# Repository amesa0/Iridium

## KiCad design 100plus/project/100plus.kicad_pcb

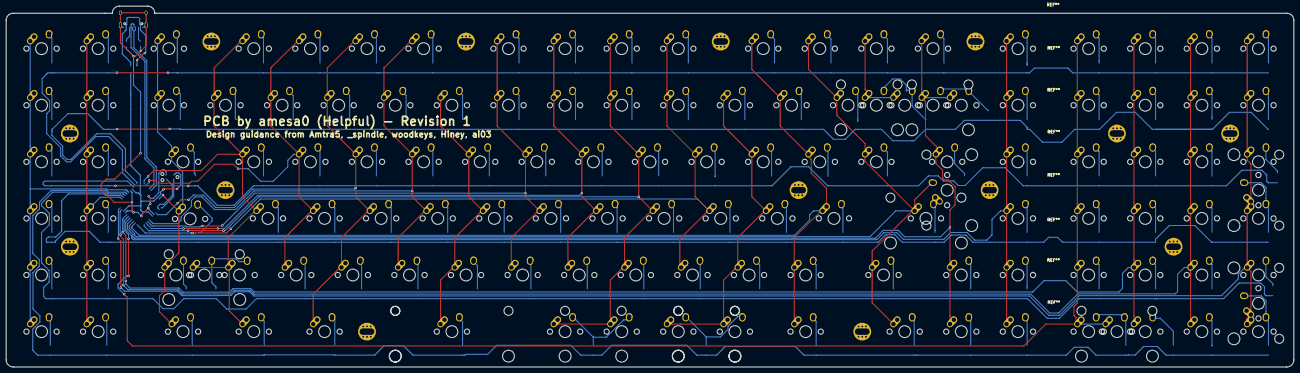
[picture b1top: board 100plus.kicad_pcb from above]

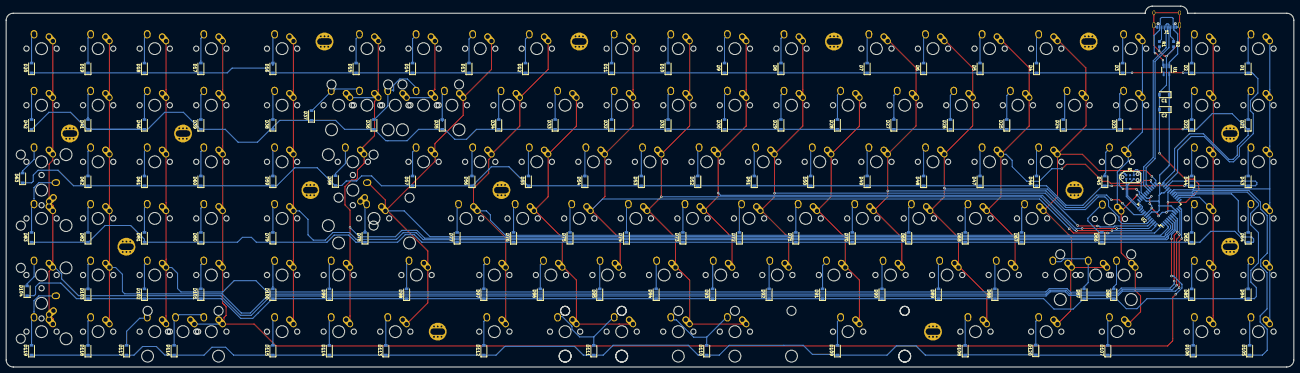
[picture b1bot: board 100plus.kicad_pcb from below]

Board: 2 copper layers, 433.4 x 121.4 mm, 258 parts (128 on the bottom side), 157 nets.

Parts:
C1: 10uf; D_SOD-123
C2: 0.4uf; D_SOD-123
D1, D2, D3, D4, D5, D6, D7, D8, D9, D10, D11, D12, D13, D14, D15, D16, D17, D18, D19, D20, D21, D22, D23, D24, D25, D26, D27, D28, D29, D30, D31, D32, D33, D34, D35, D36, D37, D38, D39, D40, D41, D42, D43, D44, D45, D46, D47, D48, D49, D50, D51, D52, D53, D54, D55, D56, D57, D58, D59, D60, D61, D62, D63, D64, D65, D66, D67, D68, D69, D70, D71, D72, D73, D74, D75, D76, D77, D78, D79, D80, D81, D82, D83, D84, D85, D86, D87, D88, D89, D90, D91, D92, D93, D94, D95, D96, D97, D98, D99, D100, D101, D102, D103, D104, D105, D106, D107, D108, D109, D110, D111, D112, D113, D114, D115, D116, D117, D118, D119, D120: D; D_SOD-123
J1: USB_Type_C_2.0_Receptacle; USB_TypeC_U31F-24SNA0201
K1, K2, K3, K4, K5, K6, K7, K8, K9, K10, K11, K12, K13, K14, K15, K16, K17, K18, K19, K20, K21, K22, K23, K24, K25, K26, K27, K28, K29, K30, K31, K32, K33, K34, K35, K36, K37, K38, K39, K40, K41, K42, K45, K46, K48, K49, K50, K51, K52, K53, K54, K55, K56, K57, K58, K59, K61, K62, K63, K64, K65, K67, K68, K70, K71, K72, K73, K74, K75, K76, K77, K78, K79, K80, K82, K83, K84, K85, K86, K87, K88, K91, K92, K93, K94, K95, K96, K97, K98, K99, K100, K102, K103, K104, K105, K106, K107, K108, K111, K112, K117, K119, K120, K121, K122, K123, K124, K125, K130: KEYSW; MX-1U-NoLED
K43, K44, K128, K129: KEYSW; MX-2U-NoLED
K47, K60, K113, K114, K118: KEYSW; MX-1.5U-NoLED
K66, K109: KEYSW; MX-2U-ReversedStabilizers-NoLED
K69, K101: KEYSW; MX-1.75U-NoLED
K81, K90: KEYSW; MX-2.25U-NoLED
K89: KEYSW; MX-1.25U-NoLED
K110: KEYSW; MX-7U-NoLED
K115, K116, K127: KEYSW; MX-3U-NoLED
K126: KEYSW; MX-6U-7UOverlay
P1: TC2030-IDC; TC2030-NL_SMALL
R1, R2: 5.1k; R_0603_1608Metric_Pad0.99x1.00mm_HandSolder
U1: MIC550X; SOT-23-5_HandSoldering
U2: ATXMEGA-A4U; TQFP-44_10x10mm_P0.8mm

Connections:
+5V: J1.A4, J1.B4, U1.1, U1.3
COL0: K1.1, K21.1, K45.1, K67.1, K87.1, K111.1, U2.17
COL1: K2.1, K22.1, K46.1, K68.1, K88.1, K112.1, U2.13
COL2: K3.1, K23.1, K47.1, K69.1, K89.1, K113.1, U2.32
COL3: K4.1, K24.1, K48.1, K70.1, K90.1, K108.1, K130.1, U2.23
COL4: K5.1, K25.1, K49.1, K71.1, K91.1, U2.24
COL5: K6.1, K26.1, K50.1, K72.1, K92.1, K114.1, U2.37
COL6: K7.1, K27.1, K51.1, K73.1, K93.1, U2.41
COL7: K8.1, K29.1, K53.1, K75.1, K95.1, U2.42
COL8: K9.1, K30.1, K54.1, K76.1, K96.1, U2.43
COL9: K10.1, K31.1, K55.1, K77.1, K97.1, K110.1, K116.1, U2.44
COL10: K11.1, K32.1, K56.1, K78.1, K98.1, U2.1
COL11: K12.1, K34.1, K58.1, K80.1, K100.1, K118.1, U2.2
COL12: K13.1, K35.1, K59.1, K81.1, K101.1, K119.1, K129.2, U2.3
COL13: K14.1, K36.1, K43.1
COL14: K15.1, K37.1, K44.1, K60.1, K102.1, K120.1, U2.4
COL15: K16.1, K38.1, K61.1, K82.1, K103.1, K121.1, U2.5
COL16: K17.1, K39.1, K62.1, K83.1, K104.1, K122.1, K128.1, U2.6
COL17: K18.1, K40.1, K63.1, K84.1, K105.1, K123.1, U2.7
COL18: K19.1, K41.1, K64.1, K85.1, K106.1, K124.1, U2.10
COL19: K20.1, K42.1, K65.1, K66.1, K86.1, K107.1, K109.1, K125.1, U2.11
GND: C1.2, C2.2, J1.A1, J1.B1, J1.S1, P1.6, R1.2, R2.2, U1.2, U2.8, U2.18, U2.30, U2.38
unnamed: D1.2, K1.2
unnamed: D2.2, K2.2
unnamed: D3.2, K3.2
unnamed: D4.2, K4.2
unnamed: D5.2, K5.2
unnamed: D6.2, K6.2
unnamed: D7.2, K7.2
unnamed: D8.2, K8.2
unnamed: D9.2, K9.2
unnamed: D10.2, K10.2
unnamed: D11.2, K11.2
unnamed: D12.2, K12.2
unnamed: D13.2, K13.2
unnamed: D14.2, K14.2
unnamed: D15.2, K15.2
unnamed: D16.2, K16.2
unnamed: D17.2, K17.2
unnamed: D18.2, K18.2
unnamed: D19.2, K19.2
unnamed: D20.2, K20.2
unnamed: D21.2, K21.2
unnamed: D22.2, K22.2
unnamed: D23.2, K23.2
unnamed: D24.2, K24.2
unnamed: D25.2, K25.2
unnamed: D26.2, K26.2
unnamed: D27.2, K27.2
unnamed: D28.2, K28.2
unnamed: D29.2, K29.2
unnamed: D30.2, K30.2
unnamed: D31.2, K31.2
unnamed: D32.2, K32.2
unnamed: D33.2, K33.2
unnamed: D34.2, K34.2
unnamed: D35.2, K35.2
unnamed: D36.2, K36.2, K43.2
unnamed: D37.2, K37.2, K44.2
unnamed: D38.2, K38.2
unnamed: D39.2, K39.2
unnamed: D40.2, K40.2
unnamed: D41.2, K41.2
unnamed: D42.2, K42.2
unnamed: D43.2, K45.2
unnamed: D44.2, K46.2
unnamed: D45.2, K47.2
unnamed: D46.2, K48.2
unnamed: D47.2, K49.2
unnamed: D48.2, K50.2
unnamed: D49.2, K51.2
unnamed: D50.2, K52.2
unnamed: D51.2, K53.2
unnamed: D52.2, K54.2
unnamed: D53.2, K55.2
unnamed: D54.2, K56.2
unnamed: D55.2, K57.2
unnamed: D56.2, K58.2
unnamed: D57.2, K59.2
unnamed: D58.2, K60.2
unnamed: D59.2, K61.2
unnamed: D60.2, K62.2
unnamed: D61.2, K63.2
unnamed: D62.2, K64.2
unnamed: D63.2, K65.2
unnamed: D64.2, K67.2
unnamed: D65.2, K68.2
unnamed: D66.2, K69.2
unnamed: D67.2, K70.2
unnamed: D68.2, K71.2
unnamed: D69.2, K72.2
unnamed: D70.2, K73.2
unnamed: D71.2, K74.2
unnamed: D72.2, K75.2
unnamed: D73.2, K76.2
unnamed: D74.2, K77.2
unnamed: D75.2, K78.2
unnamed: D76.2, K79.2
unnamed: D77.2, K80.2
unnamed: D78.2, K81.2, K129.1
unnamed: D79.2, K82.2
unnamed: D80.2, K83.2
unnamed: D81.2, K84.2
unnamed: D82.2, K85.2
unnamed: D83.2, K66.2, K86.2
unnamed: D84.2, K87.2
unnamed: D85.2, K88.2
unnamed: D86.2, K89.2
unnamed: D87.2, K90.2, K108.2
unnamed: D88.2, K91.2
unnamed: D89.2, K92.2
unnamed: D90.2, K93.2
unnamed: D91.2, K94.2
unnamed: D92.2, K95.2
unnamed: D93.2, K96.2
unnamed: D94.2, K97.2
unnamed: D95.2, K98.2
unnamed: D96.2, K99.2
unnamed: D97.2, K100.2
unnamed: D98.2, K101.2
unnamed: D99.2, K102.2
unnamed: D100.2, K103.2
unnamed: D101.2, K104.2
unnamed: D102.2, K105.2
unnamed: D103.2, K106.2
unnamed: D104.2, K107.2
unnamed: D105.2, K111.2
unnamed: D106.2, K112.2
unnamed: D107.2, K113.2
unnamed: D108.2, K114.2
unnamed: D109.2, K115.2
unnamed: D110.2, K110.2, K116.2
unnamed: D111.2, K117.2, K127.2
unnamed: D112.2, K118.2
unnamed: D113.2, K119.2
unnamed: D114.2, K120.2
unnamed: D115.2, K121.2
unnamed: D116.2, K122.2, K128.2
unnamed: D117.2, K123.2
unnamed: D118.2, K124.2
unnamed: D119.2, K109.2, K125.2
unnamed: D120.2, K130.2
unnamed: J1.A5, R2.1
unnamed: J1.A6, J1.B6, U2.27
unnamed: J1.A7, J1.B7, U2.26
unnamed: J1.B5, R1.1
unnamed: K28.1, K52.1, K74.1, K94.1, K115.1
unnamed: K33.1, K57.1, K79.1, K99.1, K117.1, K127.1
PDI: P1.1, U2.34
ROW0: D1.1, D2.1, D3.1, D4.1, D5.1, D6.1, D7.1, D8.1, D9.1, D10.1, D11.1, D12.1, D13.1, D14.1, D15.1, D16.1, D17.1, D18.1, D19.1, D20.1, U2.21
ROW1: D21.1, D22.1, D23.1, D24.1, D25.1, D26.1, D27.1, D28.1, D29.1, D30.1, D31.1, D32.1, D33.1, D34.1, D35.1, D36.1, D37.1, D38.1, D39.1, D40.1, D41.1, D42.1, U2.22
ROW2: D43.1, D44.1, D45.1, D46.1, D47.1, D48.1, D49.1, D50.1, D51.1, D52.1, D53.1, D54.1, D55.1, D56.1, D57.1, D58.1, D59.1, D60.1, D61.1, D62.1, D63.1, U2.20
ROW3: D64.1, D65.1, D66.1, D67.1, D68.1, D69.1, D70.1, D71.1, D72.1, D73.1, D74.1, D75.1, D76.1, D77.1, D78.1, D79.1, D80.1, D81.1, D82.1, D83.1, U2.14
ROW4: D84.1, D85.1, D86.1, D87.1, D88.1, D89.1, D90.1, D91.1, D92.1, D93.1, D94.1, D95.1, D96.1, D97.1, D98.1, D99.1, D100.1, D101.1, D102.1, D103.1, D104.1, U2.15
ROW5: D105.1, D106.1, D107.1, D108.1, D109.1, D110.1, D111.1, D112.1, D113.1, D114.1, D115.1, D116.1, D117.1, D118.1, D119.1, D120.1, U2.16
RST: P1.5, U2.35
VCC: C1.1, C2.1, P1.2, U1.5, U2.9, U2.19, U2.31, U2.39

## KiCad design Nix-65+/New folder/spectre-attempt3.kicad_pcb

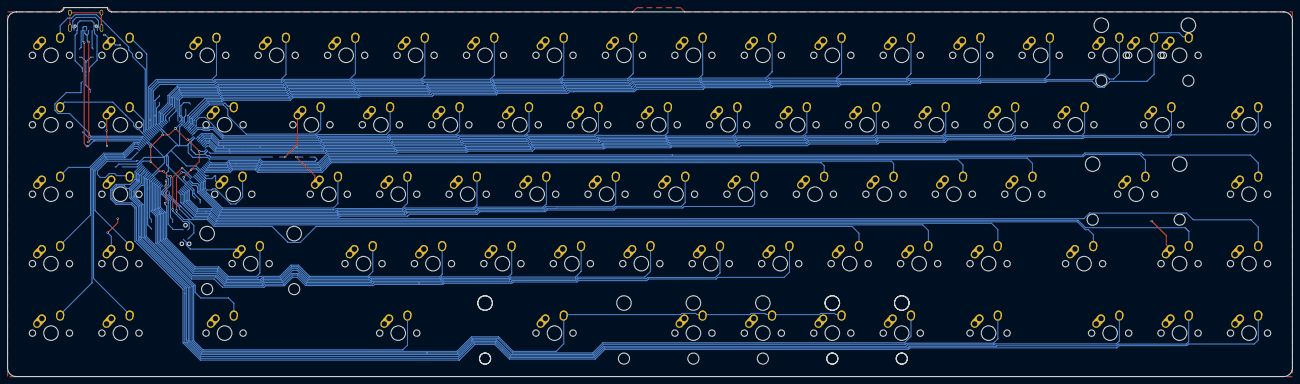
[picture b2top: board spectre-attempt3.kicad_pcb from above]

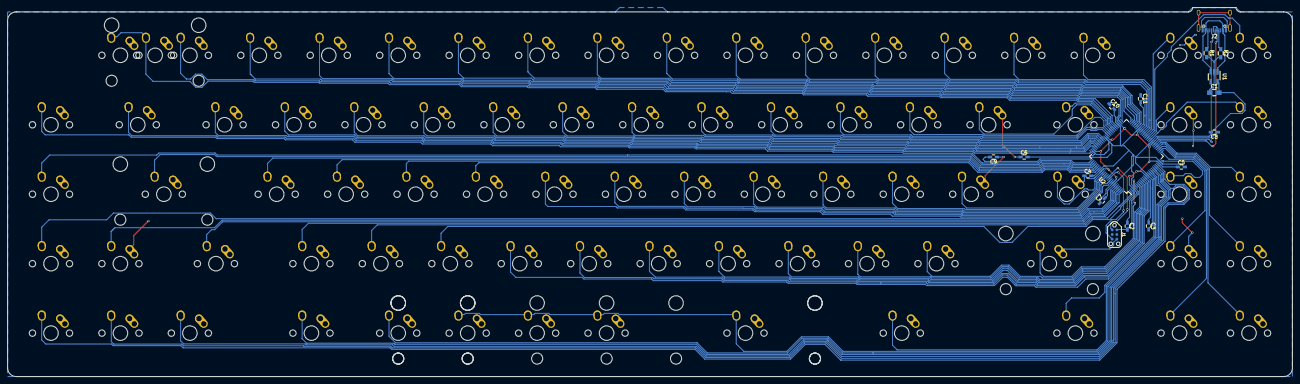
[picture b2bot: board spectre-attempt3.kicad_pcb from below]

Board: 2 copper layers, 352.4 x 101.2 mm, 98 parts (17 on the bottom side), 85 nets.

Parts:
C1: 10uF; C_0805_HandSoldering
C2, C3, C4, C5, C6, C7, C8, C9, C10, C11: 0.1uF; C_0603_HandSoldering
J1: TC2030-IDC; TC2030-NL_SMALL
J2: USB_Type_C_2.0_Receptacle; USB_TypeC_U31F-24SNA0201
K1, K2, K3, K4, K5, K6, K7, K8, K9, K10, K11, K12, K13, K14, K15, K16, K17, K19, K20, K22, K23, K24, K25, K26, K27, K28, K29, K30, K31, K32, K33, K35, K36, K37, K39, K40, K41, K42, K43, K44, K45, K46, K47, K48, K49, K51, K52, K53, K55, K56, K57, K58, K59, K60, K61, K62, K63, K64, K66, K67, K68, K69, K77, K79, K80, K81: K00; MX-1U-NoLED
K18: K00; MX-2U-ReversedStabilizers-NoLED
K21, K34, K70, K71, K78: K00; MX-1.5U-NoLED
K38, K65: K00; MX-1.75U-NoLED
K50, K54: K00; MX-2.25U-ReversedStabilizers-NoLED
K72, K73, K76: K00; MX-3U-ReversedStabilizers-NoLED
K74: K00; MX-7U-ReversedStabilizers-NoLED
K75: K00; MX-6U-7UOverlay-ReversedStabilizers
R1, R2: 5.1k; R_0603_HandSoldering
U1: MIC5504-1.2YM5; SOT-23-5_HandSoldering
U2: ATXMEGA128A1U-AU; TQFP-100_14x14mm_Pitch0.5mm

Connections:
+5V: J2.A4, J2.B4, U1.1, U1.3
/D+: J2.A6, J2.B6, U2.32
/D-: J2.A7, J2.B7, U2.31
/KEY1: K1.2, U2.37
/KEY2: K2.2, U2.38
/KEY3: K3.2, U2.39
/KEY4: K4.2, U2.40
/KEY5: K5.2, U2.41
/KEY6: K6.2, U2.42
/KEY7: K7.2, U2.45
/KEY8: K8.2, U2.46
/KEY9: K9.2, U2.47
/KEY10: K10.2, U2.48
/KEY11: K11.2, U2.49
/KEY12: K12.2, U2.50
/KEY13: K13.2, U2.51
/KEY14: K14.2, U2.52
/KEY15: K15.2, U2.55
/KEY16: K16.2, U2.56
/KEY17: K17.2, K18.2, U2.57
/KEY19: K19.2, U2.35
/KEY20: K20.2, U2.36
/KEY21: K21.2, U2.58
/KEY22: K22.2, U2.59
/KEY23: K23.2, U2.60
/KEY24: K24.2, U2.61
/KEY25: K25.2, U2.62
/KEY26: K26.2, U2.65
/KEY27: K27.2, U2.66
/KEY28: K28.2, U2.67
/KEY29: K29.2, U2.68
/KEY30: K30.2, U2.69
/KEY31: K31.2, U2.70
/KEY32: K32.2, U2.71
/KEY33: K33.2, U2.72
/KEY34: K34.2, U2.75
/KEY35: K35.2, U2.76
/KEY36: K36.2, U2.30
/KEY37: K37.2, U2.25
/KEY38: K38.2, U2.85
/KEY39: K39.2, U2.86
/KEY40: K40.2, U2.87
/KEY41: K41.2, U2.88
/KEY42: K42.2, U2.91
/KEY43: K43.2, U2.92
/KEY44: K44.2, U2.95
/KEY45: K45.2, U2.96
/KEY46: K46.2, U2.82
/KEY47: K47.2, U2.81
/KEY48: K48.2, U2.80
/KEY49: K49.2, U2.79
/KEY50: K50.2, U2.78
/KEY51: K51.2, U2.77
/KEY52: K52.2, U2.29
/KEY53: K53.2, U2.26
/KEY54: K54.2, U2.5
/KEY55: K55.2, U2.6
/KEY56: K56.2, U2.7
/KEY57: K57.2, U2.8
/KEY58: K58.2, U2.9
/KEY59: K59.2, U2.10
/KEY60: K60.2, U2.11
/KEY61: K61.2, U2.12
/KEY62: K62.2, U2.2
/KEY63: K63.2, U2.1
/KEY64: K64.2, U2.100
/KEY65: K65.2, U2.99
/KEY66: K66.2, U2.98
/KEY67: K67.2, U2.97
/KEY68: K68.2, U2.28
/KEY69: K69.2, U2.27
/KEY70: K70.2, U2.15
/KEY71: K71.2, U2.16
/KEY72: K72.2, K73.2, K74.2, K76.2, U2.17
/KEY77: K77.2, U2.18
/KEY78: K78.2, U2.19
/KEY79: K79.2, U2.20
/KEY80: K80.2, U2.21
/KEY81: K81.2, U2.22
/PDI: J1.1, U2.89
/RST: J1.5, U2.90
GND: C1.1, C2.1, C3.1, C4.1, C5.1, C6.1, C7.1, C8.1, C9.1, C10.1, C11.1, J1.6, J2.A1, J2.B1, K1.1, K2.1, K3.1, K4.1, K5.1, K6.1, K7.1, K8.1, K9.1, K10.1, K11.1, K12.1, K13.1, K14.1, K15.1, K16.1, K17.1, K18.1, K19.1, K20.1, K21.1, K22.1, K23.1, K24.1, K25.1, K26.1, K27.1, K28.1, K29.1, K30.1, K31.1, K32.1, K33.1, K34.1, K35.1, K36.1, K37.1, K38.1, K39.1, K40.1, K41.1, K42.1, K43.1, K44.1, K45.1, K46.1, K47.1, K48.1, K49.1, K50.1, K51.1, K52.1, K53.1, K54.1, K55.1, K56.1, K57.1, K58.1, K59.1, K60.1, K61.1, K62.1, K63.1, K64.1, K65.1, K66.1, K67.1, K68.1, K69.1, K70.1, K71.1, K72.1, K73.1, K74.1, K76.1, K77.1, K78.1, K79.1, K80.1, K81.1, R1.2, R2.2, U1.2, U2.3, U2.13, U2.23, U2.33, U2.43, U2.53, U2.63, U2.73, U2.84, U2.93
unnamed: J2.A5, R2.1
unnamed: J2.B5, R1.1
VCC: C1.2, C2.2, C3.2, C4.2, C5.2, C6.2, C7.2, C8.2, C9.2, C10.2, C11.2, J1.2, U1.5, U2.4, U2.14, U2.24, U2.34, U2.44, U2.54, U2.64, U2.74, U2.83, U2.94
